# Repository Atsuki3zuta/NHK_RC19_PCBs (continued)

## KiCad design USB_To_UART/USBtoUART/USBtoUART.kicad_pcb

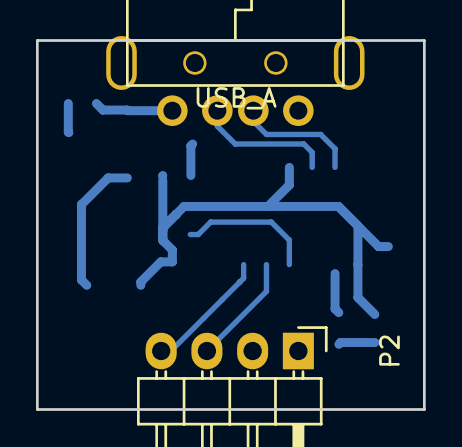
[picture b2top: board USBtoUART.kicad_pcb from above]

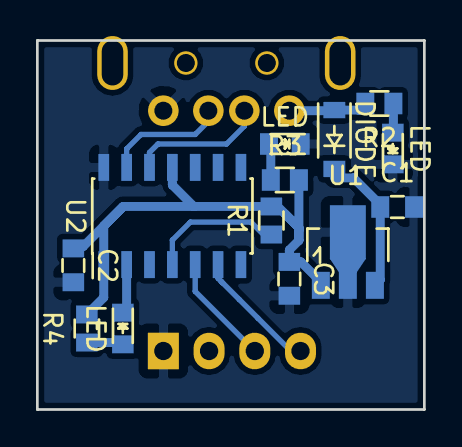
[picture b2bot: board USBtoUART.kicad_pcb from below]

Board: 2 copper layers, 21.5 x 20.5 mm, 15 parts (13 on the bottom side), 13 nets.

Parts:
C1: 10u; C_0603
C2: 0.1u; C_0603
C3: 22u; C_0603
D1: DIODE; SOD-123
D2, D3, D4: LED; LED_0603
P1: USB_A; USB-A-male
P2: CONN_01X04; Pin_Header_Angled_1x04
R1: 10k; R_0603
R2, R3, R4: R; R_0603
U1: BD33FA1; SOT89-3_Housing
U2: MCP2221A; SOIC-14_3.9x8.7mm_Pitch1.27mm

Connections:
+3.3V: C2.1, C3.1, R1.2, R3.2, R4.2, U1.1, U2.1, U2.11
+5V: D1.1, P1.1, R2.2
/D+: P1.3, U2.13
/D-: P1.2, U2.12
/GP0: D4.2, U2.2
/RX: P2.3, U2.5
/TX: P2.4, U2.6
GND: C1.2, C2.2, C3.2, D2.2, D3.2, P1.4, P2.1, U1.2, U2.14
unnamed: C1.1, D1.2, U1.3
unnamed: D2.1, R2.1
unnamed: D3.1, R3.1
unnamed: D4.1, R4.1
unnamed: R1.1, U2.4

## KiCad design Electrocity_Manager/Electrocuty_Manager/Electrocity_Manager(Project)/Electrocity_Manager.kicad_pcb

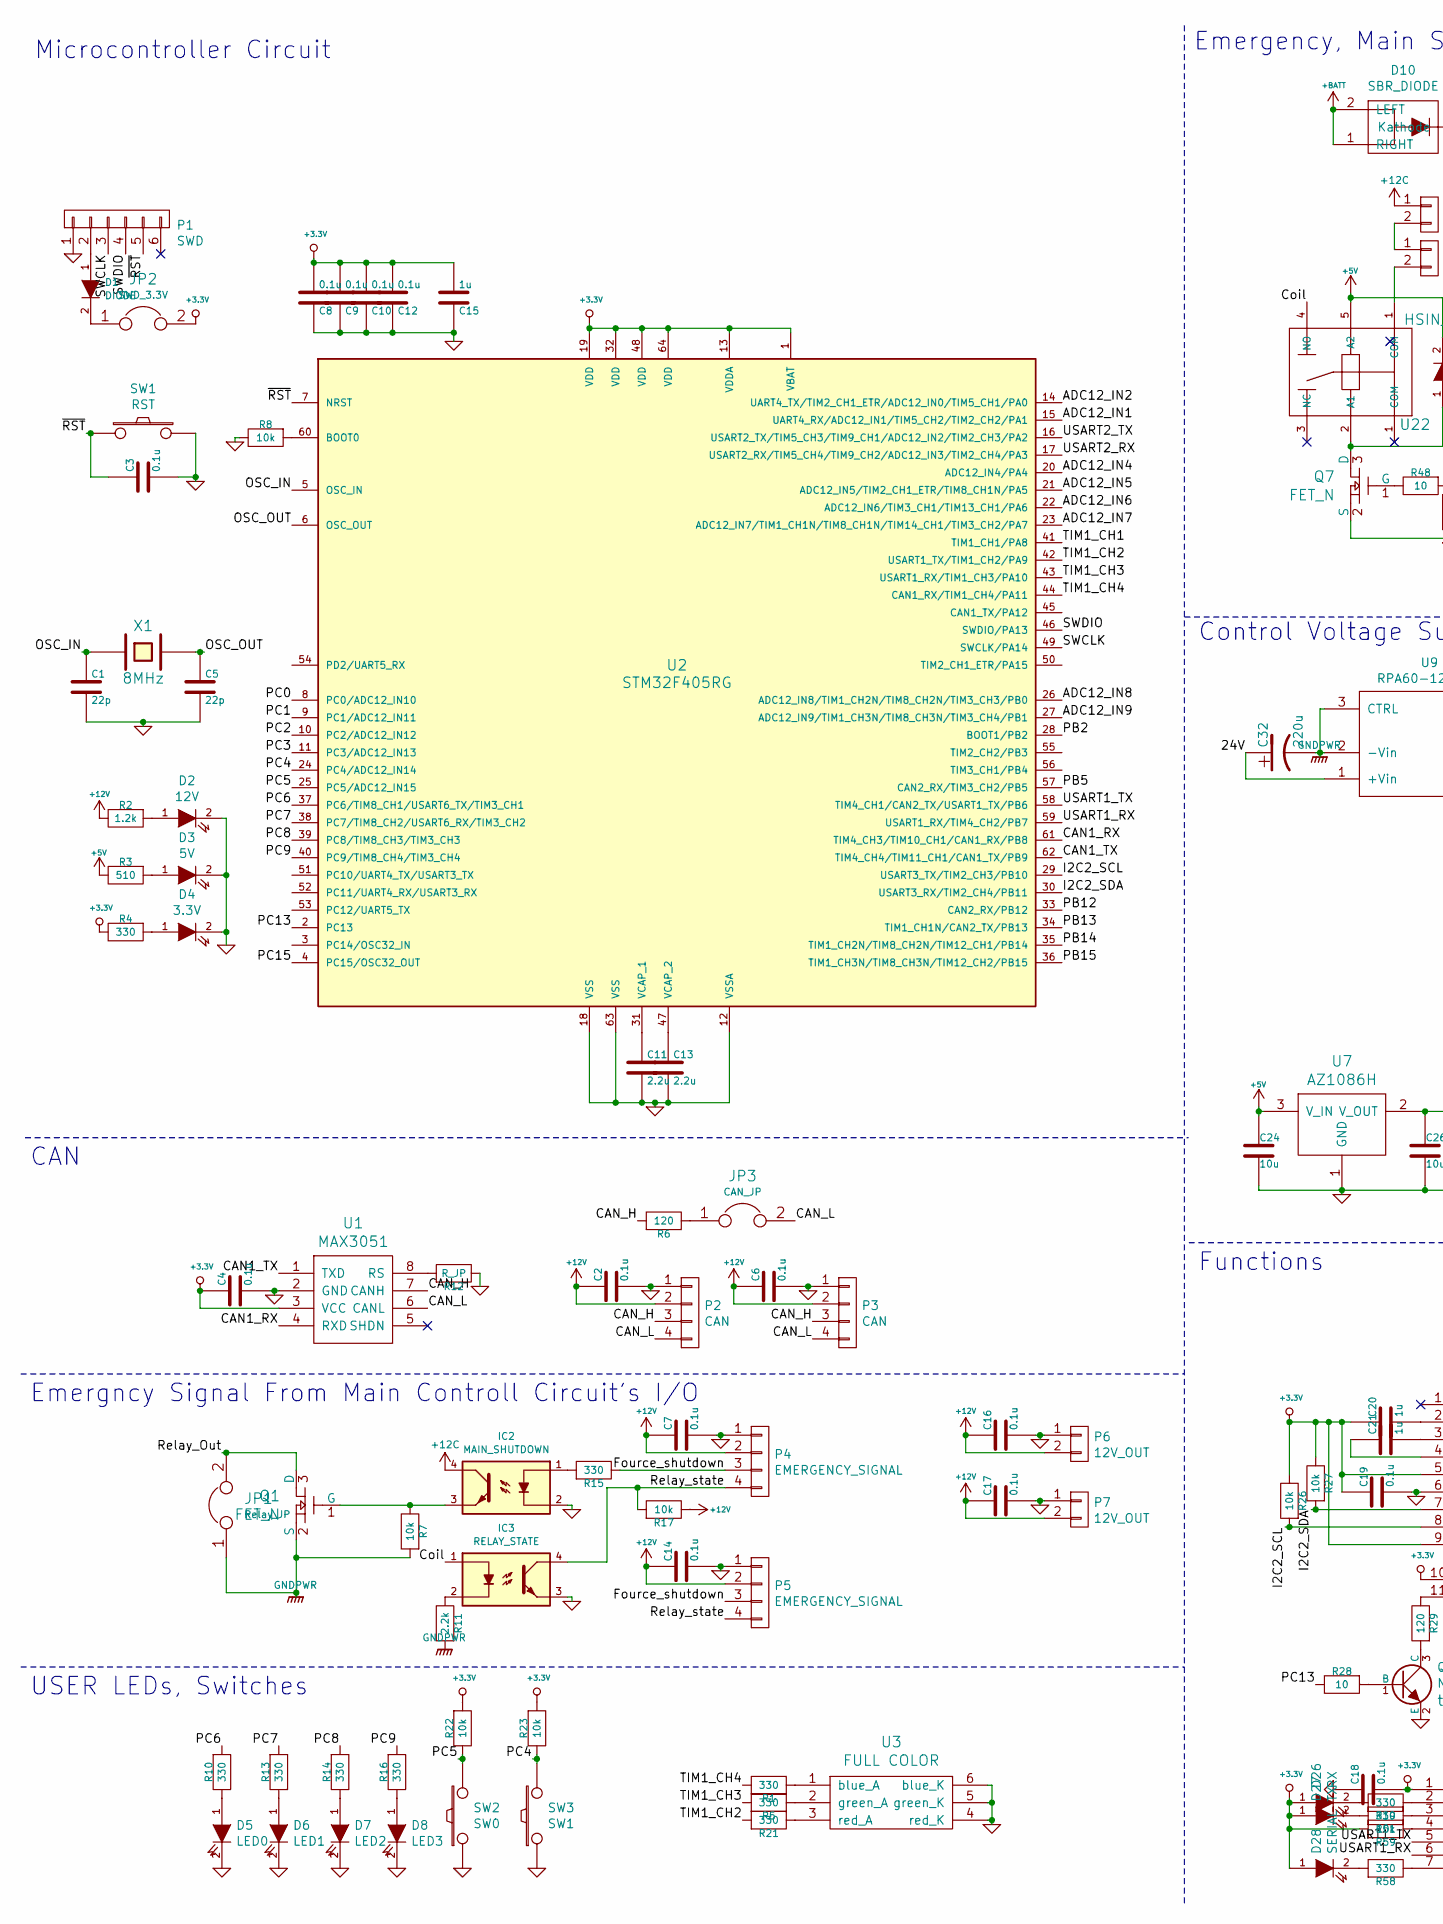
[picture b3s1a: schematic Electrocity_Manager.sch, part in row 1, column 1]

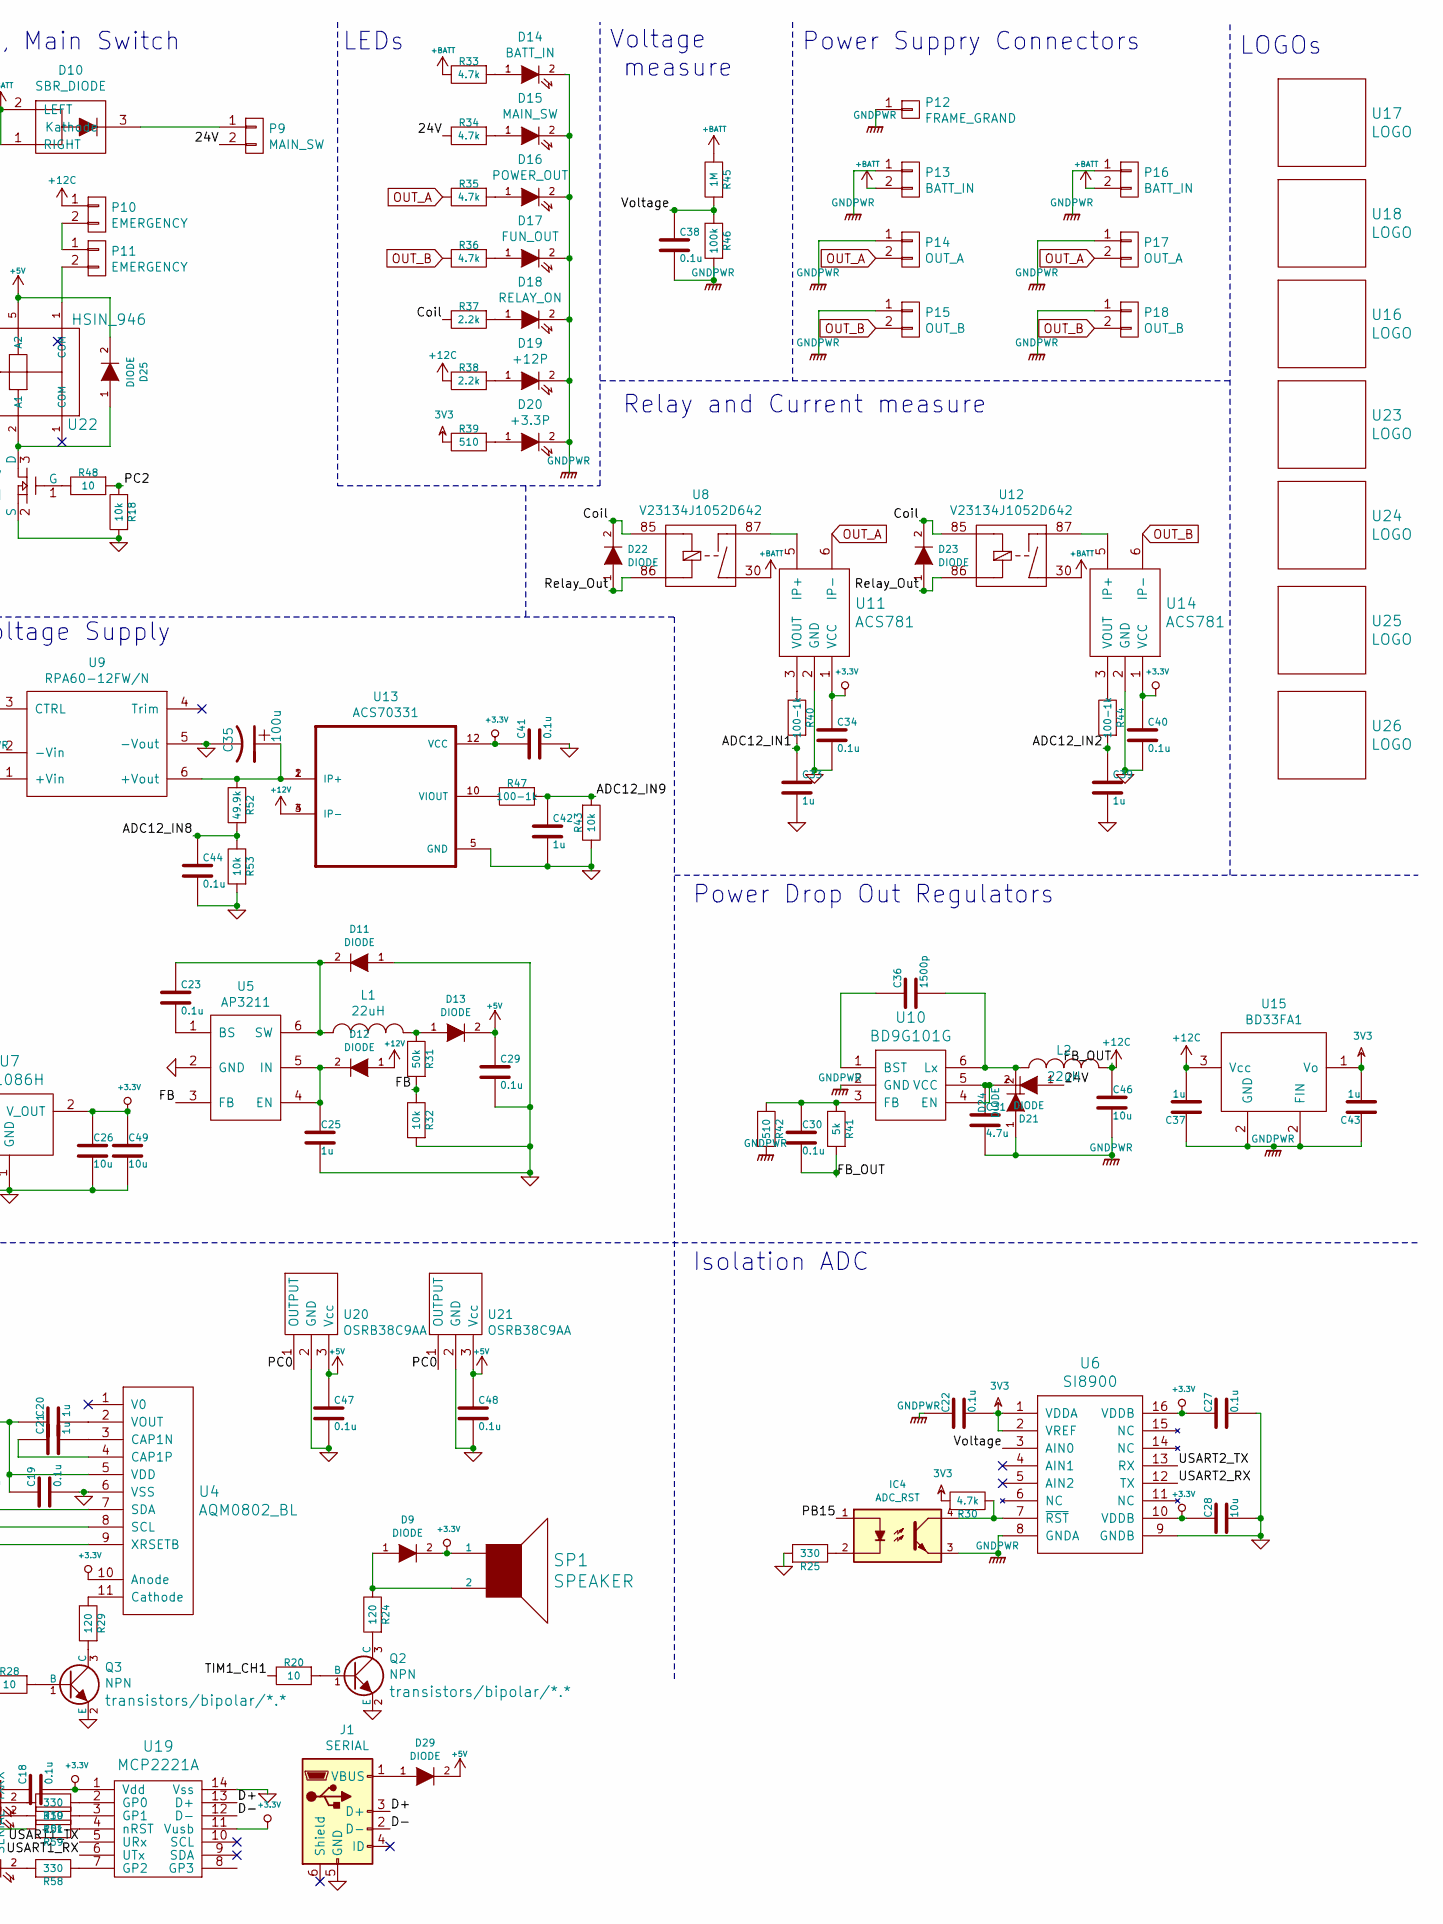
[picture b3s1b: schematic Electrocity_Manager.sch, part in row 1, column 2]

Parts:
C1, C5: 22p; C_0603
C2, C3, C4, C6, C7, C8, C9, C10, C12, C14, C16, C17, C18, C19, C22, C23, C27, C29, C30, C34, C38, C40, C41, C44, C47, C48: 0.1u; C_0603
C11, C13: 2.2u; C_0603
C15, C20, C21, C25, C33, C39, C42, C43: 1u; C_0603
C24, C26, C28, C46, C49: 10u; C_0603
C31: 4.7u; C_0603
C32: 220u; C_Radial_D6.3_L11.2_P2.5
C35: 100u; C_Radial_D6.3_L11.2_P2.5
C36: 1500p; C_0603
C37: 1u; C_0805
D1, D9, D11, D12, D13, D21, D22, D23, D24, D25, D29: DIODE; SOD-123
D2: 12V; LED_0603
D3: 5V; LED_0603
D4: 3.3V; LED_0603
D5: LED0; LED_0603
D6: LED1; LED_0603
D7: LED2; LED_0603
D8: LED3; LED_0603
D10: SBR_DIODE; TO-277A
D14: BATT_IN; LED_0603
D15: MAIN_SW; LED_0603
D16: POWER_OUT; LED_0603
D17: FUN_OUT; LED_0603
D18: RELAY_ON; LED_0603
D19: +12P; LED_0603
D20: +3.3P; LED_0603
D26: RX; LED_0603
D27: TX; LED_0603
D28: SERIAL; LED_0603
IC2: MAIN_SHUTDOWN; SOIJ-4_5.3x5.3mm_Pitch1.27mm
IC3: RELAY_STATE; SOIJ-4_5.3x5.3mm_Pitch1.27mm
IC4: ADC_RST; SOIJ-4_5.3x5.3mm_Pitch1.27mm
J1: SERIAL; USB_Micro-B_Molex_47346-0001
JP1: Relay_JP; Pin_Header_Straight_1x02
JP2: SWD_3.3V; GS2
JP3: CAN_JP; Pin_Header_Straight_1x02
L1, L2: 22uH; Inductor_Taiyo-Yuden_NR-50xx_HandSoldering
P1: SWD; ZH_6T
P2, P3: CAN; XA_4T
P4, P5: EMERGENCY_SIGNAL; XA_4T
P6, P7: 12V_OUT; XA_2T
P9: MAIN_SW; XA_2T
P10, P11: EMERGENCY; XA_2T
P12: FRAME_GRAND; SolderWirePad_single_3mmDrill
P13, P16: BATT_IN; XT90PB
P14: OUT_A; XT60_F
P15: OUT_B; XT60_F
P17: OUT_A; XT60_M
P18: OUT_B; XT60_M
Q1, Q7: FET_N; SOT-23
Q2, Q3: NPN; SOT-123
R1, R4, R5, R10, R13, R14, R15, R16, R19, R21, R25, R51, R58: 330; R_0603
R2: 1.2k; R_0603
R3, R39, R42: 510; R_0603
R6, R24, R29: 120; R_0603
R7, R8, R17, R18, R22, R23, R26, R27, R32, R43, R59: 10k; R_0603
R11, R37, R38: 2.2k; R_0603
R12: R_JP; R_0603
R20, R28, R48: 10; R_0603
R30, R33, R34, R35, R36: 4.7k; R_0603
R31: 50k; R_0603
R40, R44, R47: 100-1k; R_0603
R41: 5k; R_0603
R45: 1M; R_0805
R46: 100k; R_0805
R52: 49.9k; R_0805
R53: 10k; R_0805
SP1: SPEAKER; UGCT7525AN4
SW1: RST; SW_SPST_CK_RS282G05A3
SW2: SW0; SW_SPST_CK_RS282G05A3
SW3: SW1; SW_SPST_CK_RS282G05A3
U1: MAX3051; SOIC-8_3.9x4.9mm_Pitch1.27mm
U2: STM32F405RG; LQFP-64_10x10mm_P0.5mm
U3: FULL COLOR; OSTBABS4C2B
U4: AQM0802_BL; AQM0802_BackLight
U5: AP3211; TSOT-6-MK06A
U6: SI8900; SOIC-16_7.5x10.3mm_Pitch1.27mm
U7: AZ1086H
U8, U12: V23134J1052D642
U9: RPA60-12FW/N; RPA60-24xxSFW
U10: BD9G101G; TSOT-6-MK06A
U11, U14: ACS781
U13: ACS70331; ALLEGRO_ACS70331EESATR-005U3
U15: BD33FA1; SOT89-3_Housing
U16: LOGO; Robocon2019_30.0x30.0_silk
U17: LOGO; Power_logo_Silk_5x5
U18: LOGO; Mini_Monster
U19: MCP2221A; SOIC-14_3.9x8.7mm_Pitch1.27mm
U20, U21: OSRB38C9AA
U22: HSIN_946; relay_HSINDA_Y14H
U23: LOGO; Battery_Killer_logo
U24: LOGO; Pikatyuu_15x15
U25: LOGO; MonsterBall_10x10_silk
U26: LOGO; PiOtyu_silk_21.3x6.8
X1: 8MHz; Crystal_SMD_5032_2Pads

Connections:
3V3: C22.2, C43.2, R30.1, R39.2, U6.1 (VDDA), U6.2 (VREF), U15.1 (Vo)
+3.3V: C4.1, C8.2, C9.2, C10.2, C12.2, C15.2, C18.2, C19.1, C20.1, C26.1, C27.1, C28.1, C34.1, C40.1, C41.1, C49.1, D9.2 (K), D26.1 (A), D27.1 (A), D28.1 (A), JP2.2, R4.2, R22.1, R23.1, R26.2, R27.2, R59.1, SP1.1, U1.3 (VCC), U2.1 (VBAT), U2.13 (VDDA), U2.19 (VDD), U2.32 (VDD), U2.48 (VDD), U2.64 (VDD), U4.5 (VDD), U4.9 (XRSETB), U4.10 (Anode), U6.10 (VDDB), U6.16 (VDDB), U7.2 (V_OUT), U11.1 (VCC), U13.12 (VCC), U14.1 (VCC), U19.1 (Vdd), U19.11 (Vusb)
+5V: C24.1, C29.1, C47.1, C48.1, D13.2 (K), D25.2 (K), D29.2 (K), R3.2, U7.3 (V_IN), U20.3 (Vcc), U21.3 (Vcc), U22.5 (A2)
+12C: C30.2, C37.2, C46.1, IC2.4, L2.2, P10.1, R38.2, R41.1, U15.3 (Vcc)
+12V: C2.1, C6.1, C7.1, C14.1, C16.1, C17.1, D12.1 (A), P2.2, P3.2, P4.2, P5.2, P6.2, P7.2, R2.2, R17.2, U13.3 (IP-), U13.4 (IP-)
+BATT: D10.1 (RIGHT), D10.2 (LEFT), P13.2, P16.2, R33.2, R45.2, U8.30, U12.30
/24V: C32.1, D21.1 (A), P9.2, R34.2, U9.1 (+Vin)
/ADC12_IN1: C33.1, R40.1, U2.15 (UART4_RX/ADC12_IN1/TIM5_CH2/TIM2_CH2/PA1)
/ADC12_IN2: C39.1, R44.1, U2.14 (UART4_TX/TIM2_CH1_ETR/ADC12_IN0/TIM5_CH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)
/ADC12_IN4: U2.20 (ADC12_IN4/PA4)
/ADC12_IN5: U2.21 (ADC12_IN5/TIM2_CH1_ETR/TIM8_CH1N/PA5)
/ADC12_IN6: U2.22 (ADC12_IN6/TIM3_CH1/TIM13_CH1/PA6)
/ADC12_IN7: U2.23 (ADC12_IN7/TIM1_CH1N/TIM8_CH1N/TIM14_CH1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)
/ADC12_IN8: C44.1, R52.1, R53.2, U2.26 (ADC12_IN8/TIM1_CH2N/TIM8_CH2N/TIM3_CH3/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)
/ADC12_IN9: C42.1, R43.1, R47.1, U2.27 (ADC12_IN9/TIM1_CH3N/TIM8_CH3N/TIM3_CH4/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)
/CAN1_RX: U1.4 (RXD), U2.61 (TIM4_CH3/TIM10_CH1/CAN1_RX/PB8)
/CAN1_TX: U1.1 (TXD), U2.62 (TIM4_CH4/TIM11_CH1/CAN1_TX/PB9)
/CAN_H: P2.3, P3.3, R6.1, U1.7 (CANH)
/CAN_L: JP3.2, P2.4, P3.4, U1.6 (CANL)
/Coil: D22.2 (K), D23.2 (K), IC3.1, R37.2, U8.85, U12.85, U22.4 (NO)
/D+: J1.3 (D+), U19.13 (D+)
/D-: J1.2 (D-), U19.12 (D-)
/FB: R31.1, R32.2, U5.3 (FB)
/Fource_shutdown: P4.3, P5.3, R15.2
/I2C2_SCL: R26.1, U2.29 (USART3_TX/TIM2_CH3/PB10), U4.8 (SCL)
/I2C2_SDA: R27.1, U2.30 (USART3_RX/TIM2_CH4/PB11), U4.7 (SDA)
/OSC_IN: C1.1, U2.5 (OSC_IN), X1.1
/OSC_OUT: C5.1, U2.6 (OSC_OUT), X1.2
/PB2: U2.28 (BOOT1/PB2)
/PB5: U2.57 (CAN2_RX/TIM3_CH2/PB5)
/PB12: U2.33 (CAN2_RX/PB12)
/PB13: U2.34 (TIM1_CH1N/CAN2_TX/PB13)
/PB14: U2.35 (TIM1_CH2N/TIM8_CH2N/TIM12_CH1/PB14)
/PB15: IC4.1, U2.36 (TIM1_CH3N/TIM8_CH3N/TIM12_CH2/PB15)
/PC0: U2.8 (PC0/ADC12_IN10), U20.1 (OUTPUT), U21.1 (OUTPUT)
/PC1: U2.9 (PC1/ADC12_IN11)
/PC2: R18.2, R48.1, U2.10 (PC2/ADC12_IN12)
/PC3: U2.11 (PC3/ADC12_IN13)
/PC4: R23.2, SW3.2, U2.24 (PC4/ADC12_IN14)
/PC5: R22.2, SW2.2, U2.25 (PC5/ADC12_IN15)
/PC6: R10.1, U2.37 (PC6/TIM8_CH1/USART6_TX/TIM3_CH1)
/PC7: R13.1, U2.38 (PC7/TIM8_CH2/USART6_RX/TIM3_CH2)
/PC8: R14.1, U2.39 (PC8/TIM8_CH3/TIM3_CH3)
/PC9: R16.1, U2.40 (PC9/TIM8_CH4/TIM3_CH4)
/PC13: R28.2, U2.2 (PC13)
/PC15: U2.4 (PC15/OSC32_OUT)
/Relay_Out: D22.1 (A), D23.1 (A), JP1.2, Q1.3 (D), U8.86, U12.86
/Relay_state: IC3.4, P4.4, P5.4, R17.1
/SWCLK: P1.3, U2.49 (SWCLK/PA14)
/SWDIO: P1.4, U2.46 (SWDIO/PA13)
/TIM1_CH1: R20.2, U2.41 (TIM1_CH1/PA8)
/TIM1_CH2: R21.1, U2.42 (USART1_TX/TIM1_CH2/PA9)
/TIM1_CH3: R5.1, U2.43 (USART1_RX/TIM1_CH3/PA10)
/TIM1_CH4: R1.1, U2.44 (CAN1_RX/TIM1_CH4/PA11)
/USART1_RX: U2.59 (USART1_RX/TIM4_CH2/PB7), U19.6 (UTx)
/USART1_TX: U2.58 (TIM4_CH1/CAN2_TX/USART1_TX/PB6), U19.5 (URx)
/USART2_RX: U2.17 (USART2_RX/TIM5_CH4/TIM9_CH2/ADC12_IN3/T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), U6.12 (TX)
/USART2_TX: U2.16 (USART2_TX/TIM5_CH3/TIM9_CH1/ADC12_IN2/T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), U6.13 (RX)
/Voltage: C38.1, R45.1, R46.2, U6.3 (AIN0)
/~RST: C3.1, P1.5, SW1.1, U2.7 (NRST)
GND: C1.2, C2.2, C3.2, C4.2, C5.2, C6.2, C7.2, C8.1, C9.1, C10.1, C11.2, C12.1, C13.2, C14.2, C15.1, C16.2, C17.2, C18.1, C19.2, C24.2, C25.2, C26.2, C27.2, C28.2, C29.2, C33.2, C34.2, C35.2, C39.2, C40.2, C41.2, C42.2, C44.2, C47.2, C48.2, C49.2, D2.2 (K), D3.2 (K), D4.2 (K), D5.2 (K), D6.2 (K), D7.2 (K), D8.2 (K), D11.1 (A), IC2.2, IC3.3, J1.5 (GND), P1.1, P2.1, P3.1, P4.1, P5.1, P6.1, P7.1, Q2.2 (E), Q3.2 (E), Q7.2 (S), R8.2, R12.2, R18.1, R25.1, R32.1, R43.2, R53.1, SW1.2, SW2.1, SW3.1, U1.2 (GND), U2.12 (VSSA), U2.18 (VSS), U2.63 (VSS), U3.4 (red_K), U3.5 (green_K), U3.6 (blue_K), U4.6 (VSS), U5.2 (GND), U6.9 (GNDB), U7.1 (GND), U9.5 (-Vout), U11.2 (GND), U13.5 (GND), U14.2 (GND), U19.14 (Vss), U20.2 (GND), U21.2 (GND)
GNDPWR: C22.1, C31.2, C32.2, C37.1, C38.2, C43.1, C46.2, D14.2 (K), D15.2 (K), D16.2 (K), D17.2 (K), D18.2 (K), D19.2 (K), D20.2 (K), D24.1 (A), IC4.3, JP1.1, P12.1, P13.1, P14.1, P15.1, P16.1, P17.1, P18.1, Q1.2 (S), R7.1, R11.1, R42.1, R46.1, U6.8 (GNDA), U9.2 (-Vin), U9.3 (CTRL), U10.2 (GND), U15.2 (FIN)
unnamed: C11.1, U2.31 (VCAP_1)
unnamed: C13.1, U2.47 (VCAP_2)
unnamed: C20.2, U4.2 (VOUT)
unnamed: C21.1, U4.4 (CAP1P)
unnamed: C21.2, U4.3 (CAP1N)
unnamed: C23.1, D11.2 (K), L1.1, U5.6 (SW)
unnamed: C23.2, U5.1 (BS)
unnamed: C25.1, D12.2 (K), U5.4 (EN), U5.5 (IN)
unnamed: C30.1, R41.2, R42.2, U10.3 (FB)
unnamed: C31.1, D21.2 (K), U10.4 (EN), U10.5 (VCC)
unnamed: C35.1, R52.2, U9.6 (+Vout), U13.1 (IP+), U13.2 (IP+)
unnamed: C36.1, U10.1 (BST)
unnamed: C36.2, D24.2 (K), L2.1, U10.6 (Lx)
unnamed: D1.1 (A), P1.2
unnamed: D1.2 (K), JP2.1
unnamed: D2.1 (A), R2.1
unnamed: D3.1 (A), R3.1
unnamed: D4.1 (A), R4.1
unnamed: D5.1 (A), R10.2
unnamed: D6.1 (A), R13.2
unnamed: D7.1 (A), R14.2
unnamed: D8.1 (A), R16.2
unnamed: D9.1 (A), R24.2, SP1.2
unnamed: D10.3 (Kathode), P9.1
unnamed: D13.1 (A), L1.2, R31.2
unnamed: D14.1 (A), R33.1
unnamed: D15.1 (A), R34.1
unnamed: D16.1 (A), R35.1
unnamed: D17.1 (A), R36.1
unnamed: D18.1 (A), R37.1
unnamed: D19.1 (A), R38.1
unnamed: D20.1 (A), R39.1
unnamed: D25.1 (A), Q7.3 (D), U22.2 (A1)
unnamed: D26.2 (K), R19.1
unnamed: D27.2 (K), R51.1
unnamed: D28.2 (K), R58.1
unnamed: D29.1 (A), J1.1 (VBUS)
unnamed: IC2.1, R15.1
unnamed: IC2.3, Q1.1 (G), R7.2
unnamed: IC3.2, R11.2
unnamed: IC4.2, R25.2
unnamed: IC4.4, R30.2, U6.7 (~RST~)
unnamed: JP3.1, R6.2
unnamed: P10.2, P11.1
unnamed: P11.2, U22.1 (COM)
unnamed: Q2.1 (B), R20.1
unnamed: Q2.3 (C), R24.1
unnamed: Q3.1 (B), R28.1
unnamed: Q3.3 (C), R29.1
unnamed: Q7.1 (G), R48.2
unnamed: R1.2, U3.1 (blue_A)
unnamed: R5.2, U3.2 (green_A)
unnamed: R8.1, U2.60 (BOOT0)
unnamed: R12.1, U1.8 (RS)
unnamed: R19.2, U19.2 (GP0)
unnamed: R21.2, U3.3 (red_A)
unnamed: R29.2, U4.11 (Cathode)
unnamed: R40.2, U11.3 (VOUT)
unnamed: R44.2, U14.3 (VOUT)
unnamed: R47.2, U13.10 (VIOUT)
unnamed: R51.2, U19.3 (GP1)
unnamed: R58.2, U19.7 (GP2)
unnamed: R59.2, U19.4 (nRST)
unnamed: U8.87, U11.5 (IP+)
unnamed: U12.87, U14.5 (IP+)
OUT_A: P14.2, P17.2, R35.2, U11.6 (IP-)
OUT_B: P15.2, P18.2, R36.2, U14.6 (IP-)

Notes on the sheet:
USER LEDs, Switches
Emergncy Signal From Main Controll Circuit's I/O
CAN
Functions
Microcontroller Circuit
LOGOs
Power Suppry Connectors
LEDs
Relay and Current measure
Voltage measure
Emergency, Main Switch
Isolation ADC
Power Drop Out Regulators
Control Voltage Supply

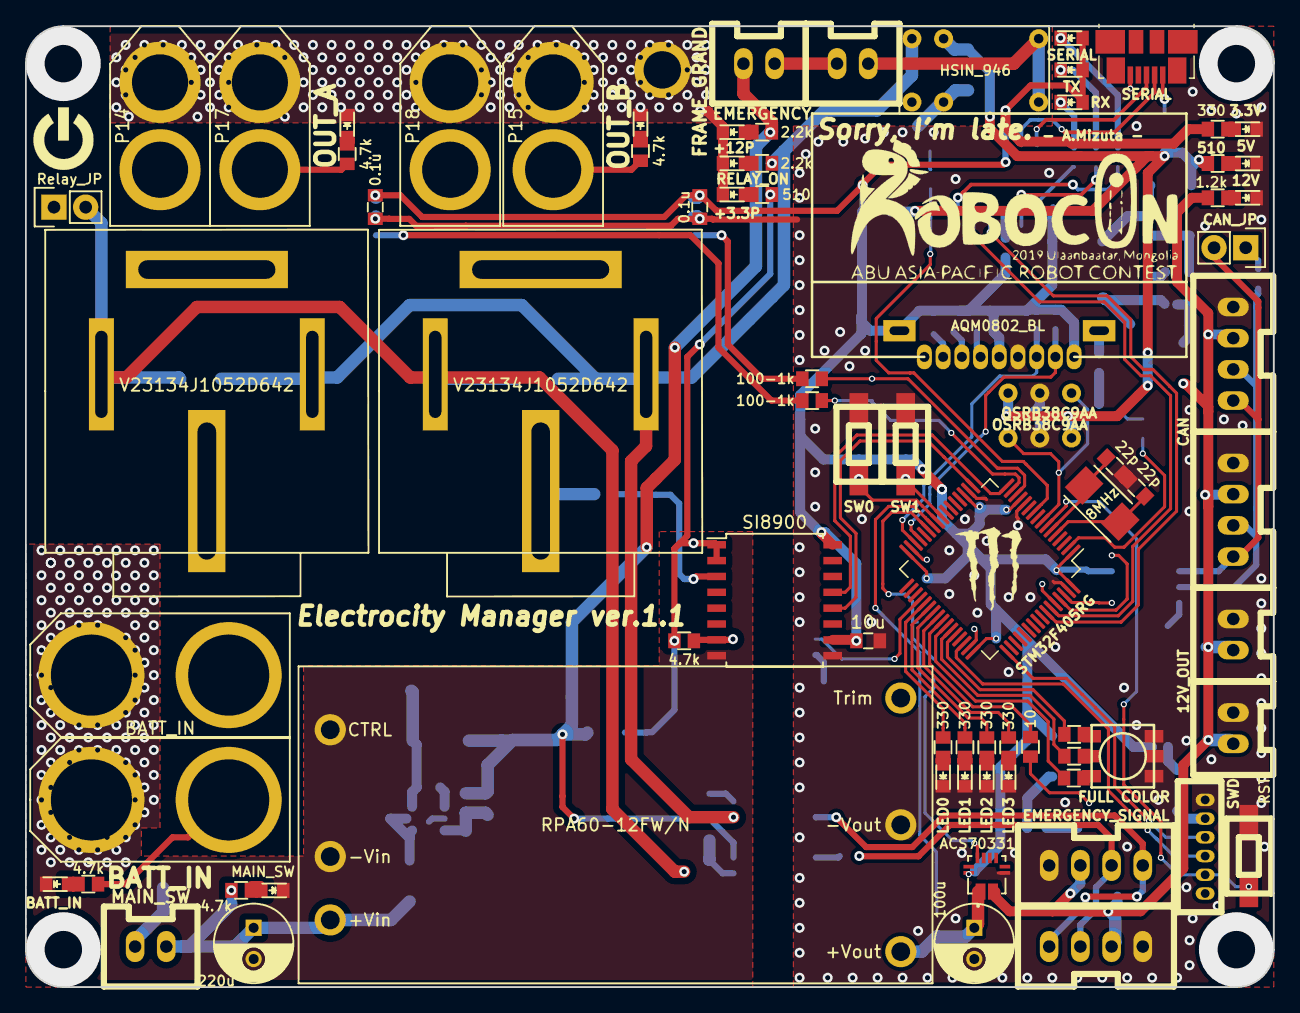
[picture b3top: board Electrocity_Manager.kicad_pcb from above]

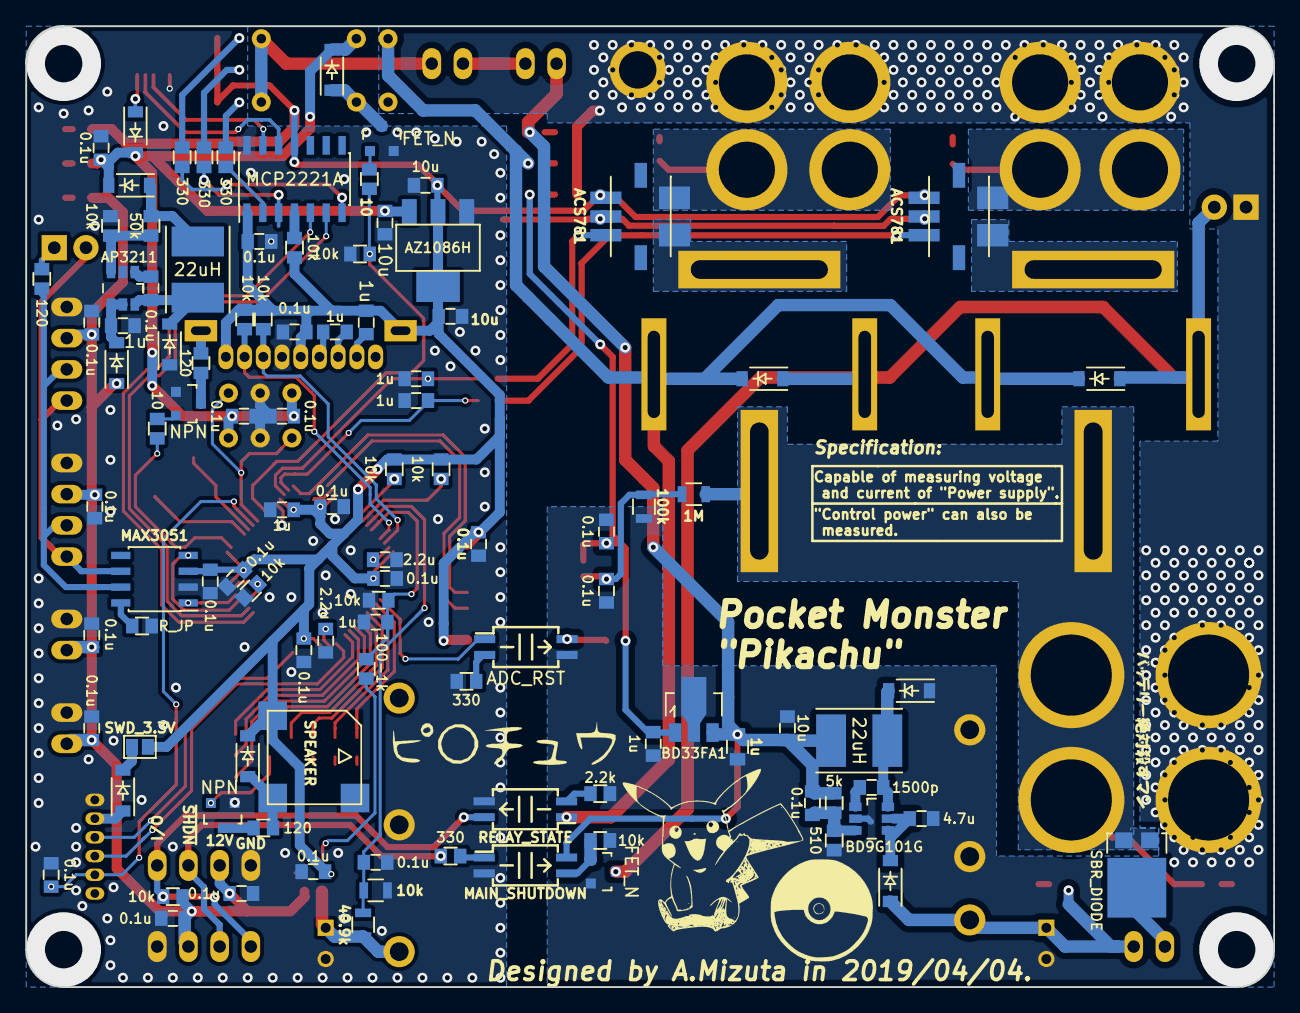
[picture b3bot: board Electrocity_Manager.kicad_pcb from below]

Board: 2 copper layers, 100.0 x 77.0 mm, 190 parts (107 on the bottom side), 117 nets.

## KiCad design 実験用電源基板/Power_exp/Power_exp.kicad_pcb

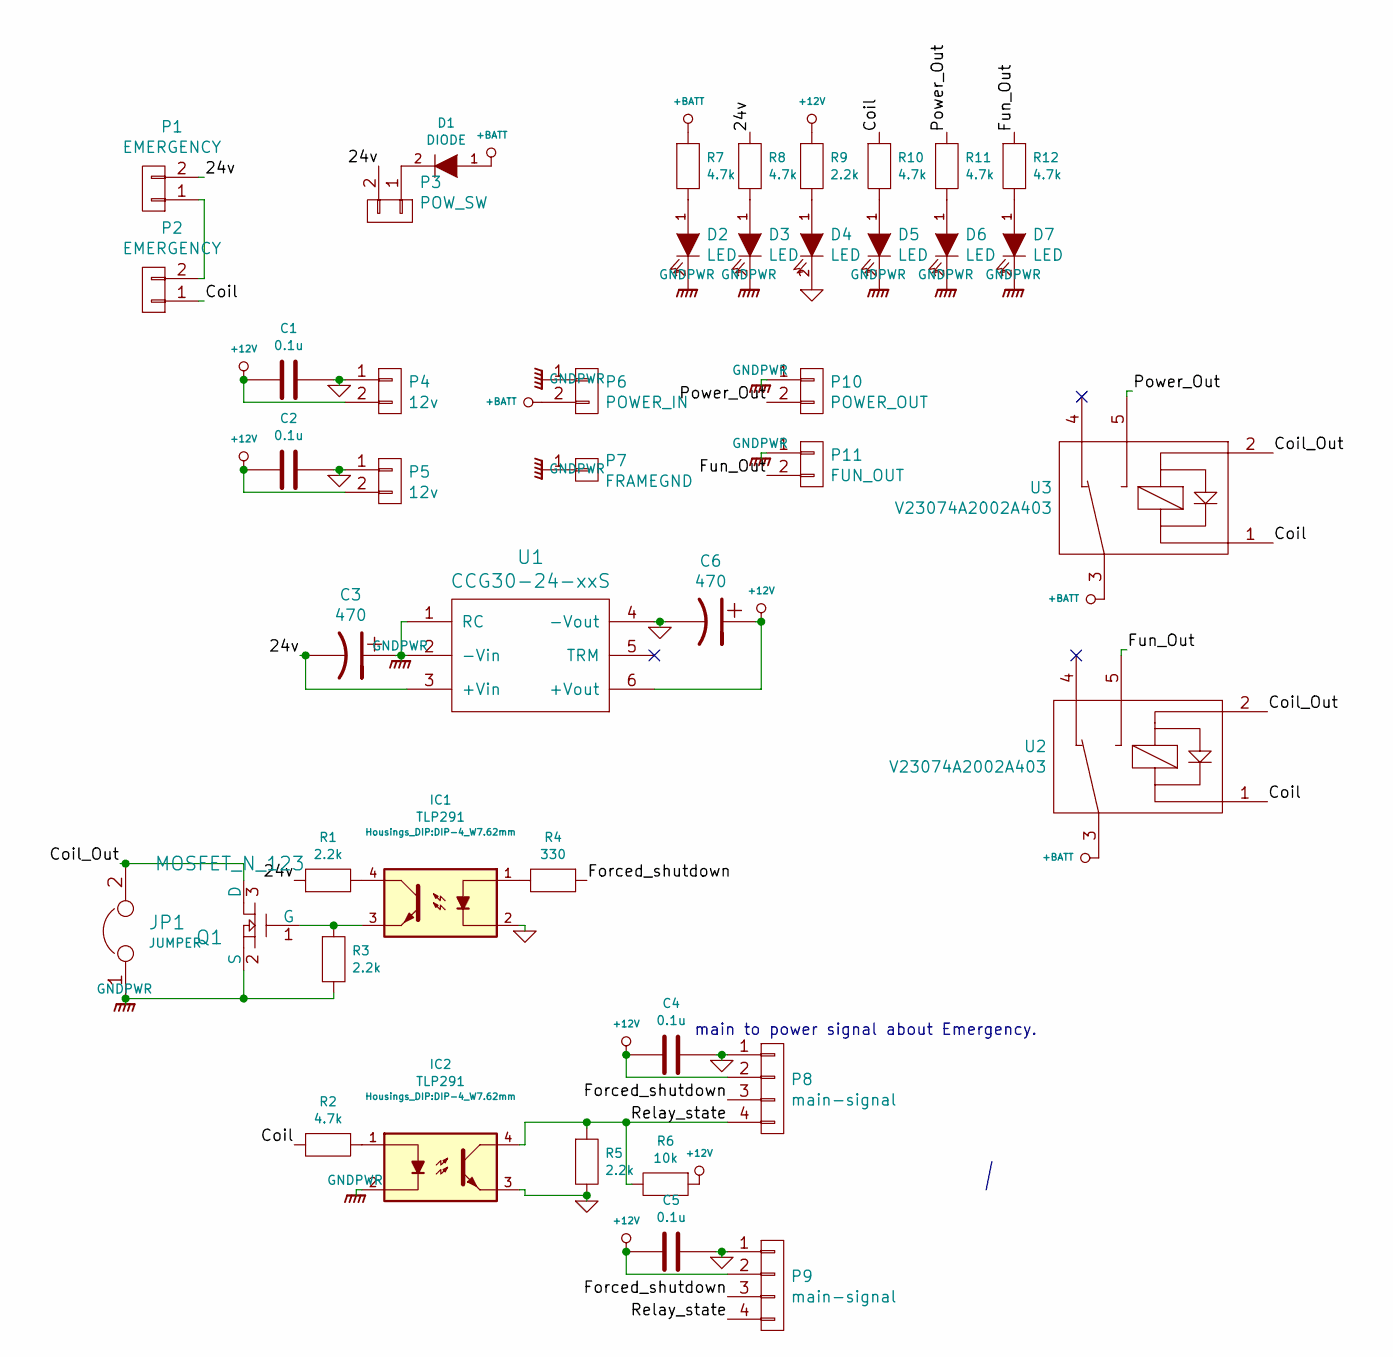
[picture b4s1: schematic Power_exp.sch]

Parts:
C1, C2, C4, C5: 0.1u; C_0603
C3, C6: 470; C_Radial_D10_L20_P5
D1: DIODE; SMB_Handsoldering
D2, D3, D4, D5, D6, D7: LED; LED-3MM
IC1, IC2: TLP291; DIP-4_W7.62mm
JP1: JUMPER; Pin_Header_Straight_1x02
P1, P2: EMERGENCY; XA_2T
P3: POW_SW; XA_2T
P4, P5: 12v; XA_2T
P6: POWER_IN; XT60_T
P7: FRAMEGND; SolderWirePad_single_2mmDrill
P8: main-signal; XA_4T
P9: main-signal; XA_4L
P10: POWER_OUT; XT60_T
P11: FUN_OUT; XT60_T
Q1: MOSFET_N_123; SOT-23_Handsoldering
R1, R3, R5, R9: 2.2k; R_0603
R2, R7, R8, R10, R11, R12: 4.7k; R_0603
R4: 330; R_0603
R6: 10k; R_0603
U1: CCG30-24-xxS
U2, U3: V23074A2002A403

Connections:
+12V: C1.1, C2.1, C4.2, C5.2, C6.1, P4.2, P5.2, P8.2, P9.2, R6.1, R9.1, U1.6 (+Vout)
+BATT: D1.1 (A), P6.2, R7.1, U2.3, U3.3
/24v: C3.2, P1.2, P3.2, R1.1, R8.1, U1.3 (+Vin)
/Coil: P2.1, R2.2, R10.1, U2.1, U3.1
/Coil_Out: JP1.2, Q1.3 (D), U2.2, U3.2
/Forced_shutdown: P8.3, P9.3, R4.1
/Fun_Out: P11.2, R12.1, U2.5
/Power_Out: P10.2, R11.1, U3.5
/Relay_state: IC2.4, P8.4, P9.4, R5.1, R6.2
GND: C1.2, C2.2, C4.1, C5.1, C6.2, D4.2 (K), IC1.2, IC2.3, P4.1, P5.1, P8.1, P9.1, R5.2, U1.4 (-Vout)
GNDPWR: C3.1, D2.2 (K), D3.2 (K), D5.2 (K), D6.2 (K), D7.2 (K), IC2.2, JP1.1, P6.1, P7.1, P10.1, P11.1, Q1.2 (S), R3.2, U1.1 (RC), U1.2 (-Vin)
unnamed: D1.2 (K), P3.1
unnamed: D2.1 (A), R7.2
unnamed: D3.1 (A), R8.2
unnamed: D4.1 (A), R9.2
unnamed: D5.1 (A), R10.2
unnamed: D6.1 (A), R11.2
unnamed: D7.1 (A), R12.2
unnamed: IC1.1, R4.2
unnamed: IC1.3, Q1.1 (G), R3.1
unnamed: IC1.4, R1.2
unnamed: IC2.1, R2.1
unnamed: P1.1, P2.2

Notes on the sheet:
main to power signal about Emergency.

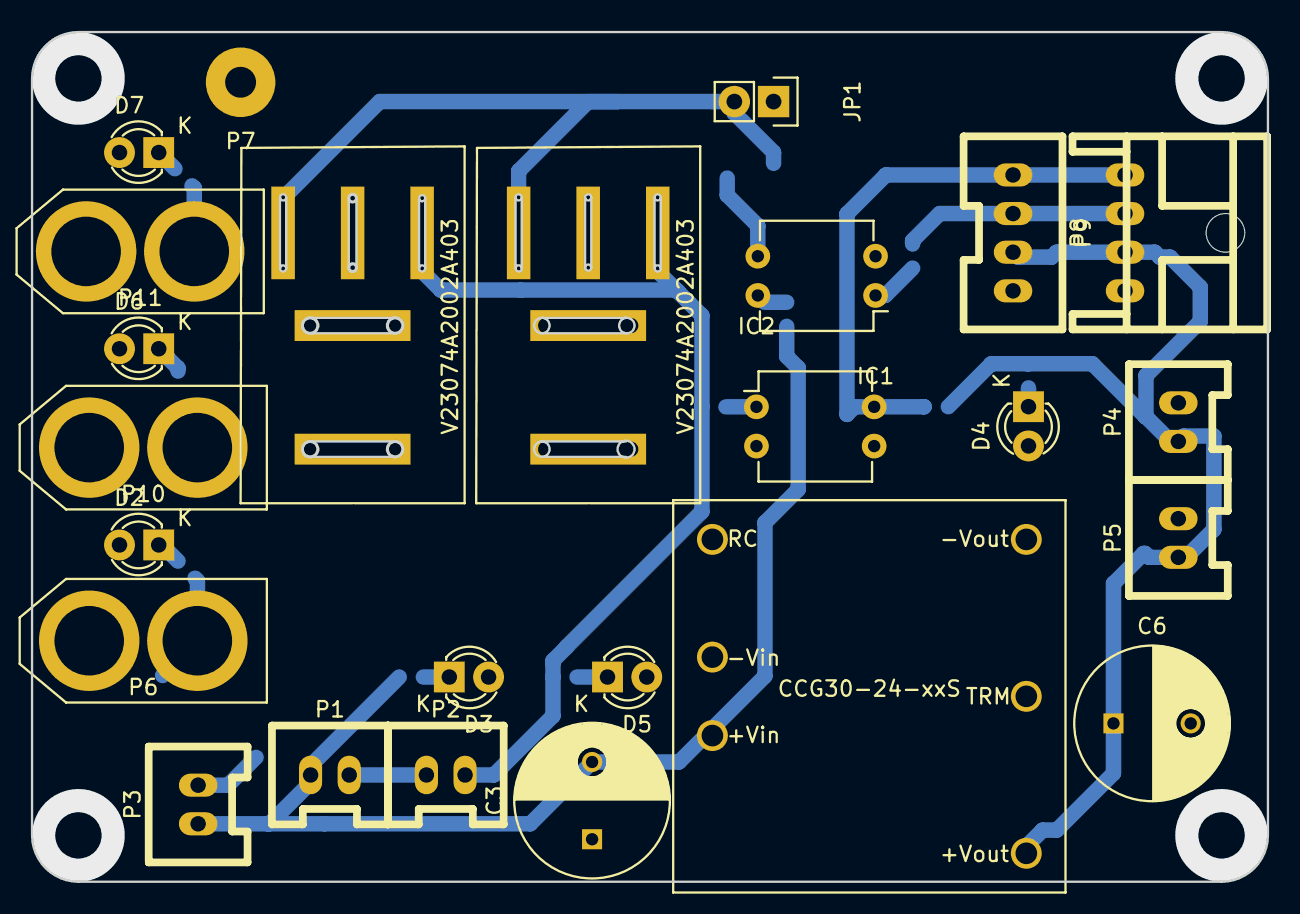
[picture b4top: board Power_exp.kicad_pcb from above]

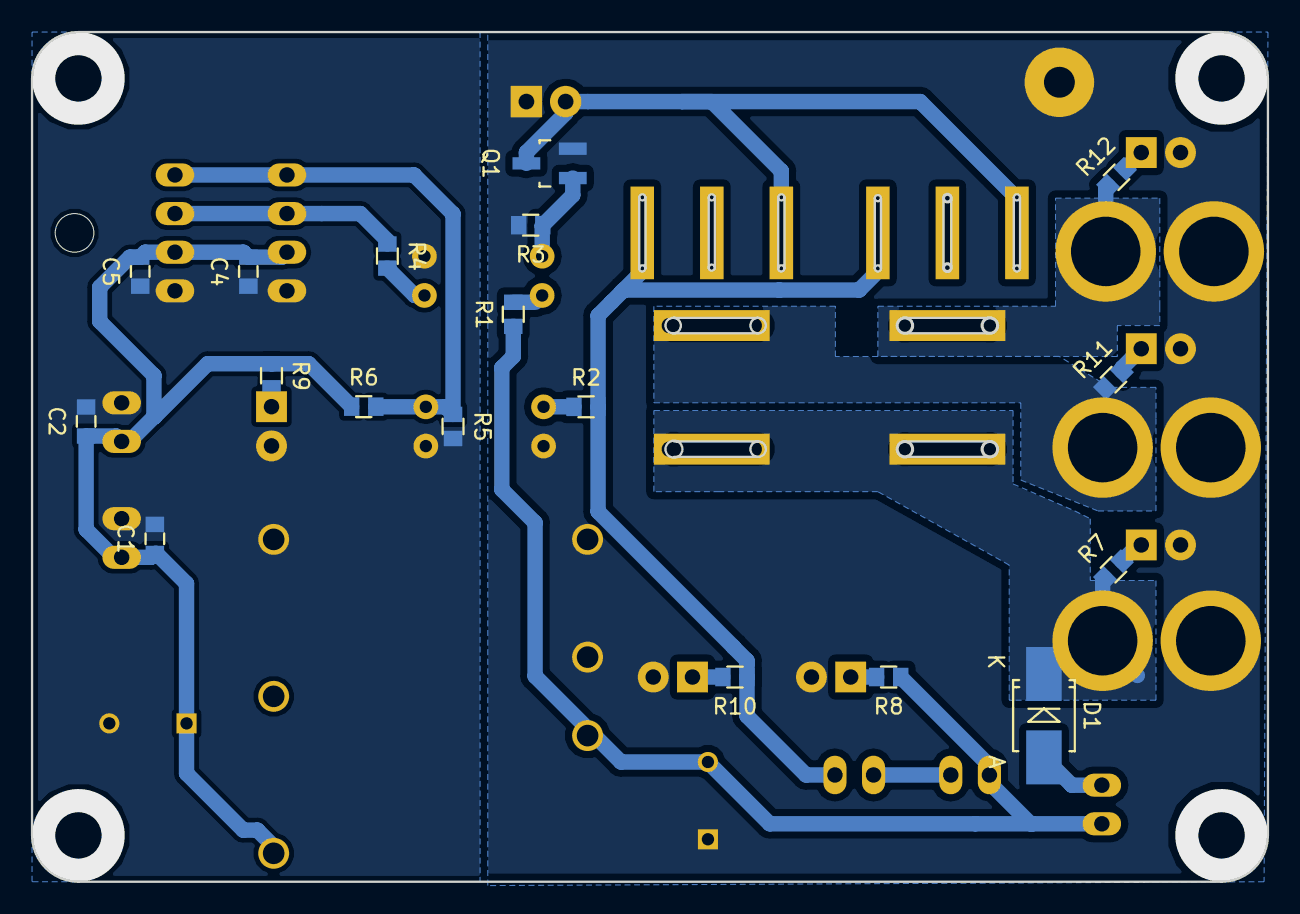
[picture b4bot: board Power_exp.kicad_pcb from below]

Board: 2 copper layers, 80.0 x 55.0 mm, 43 parts (18 on the bottom side), 23 nets.
